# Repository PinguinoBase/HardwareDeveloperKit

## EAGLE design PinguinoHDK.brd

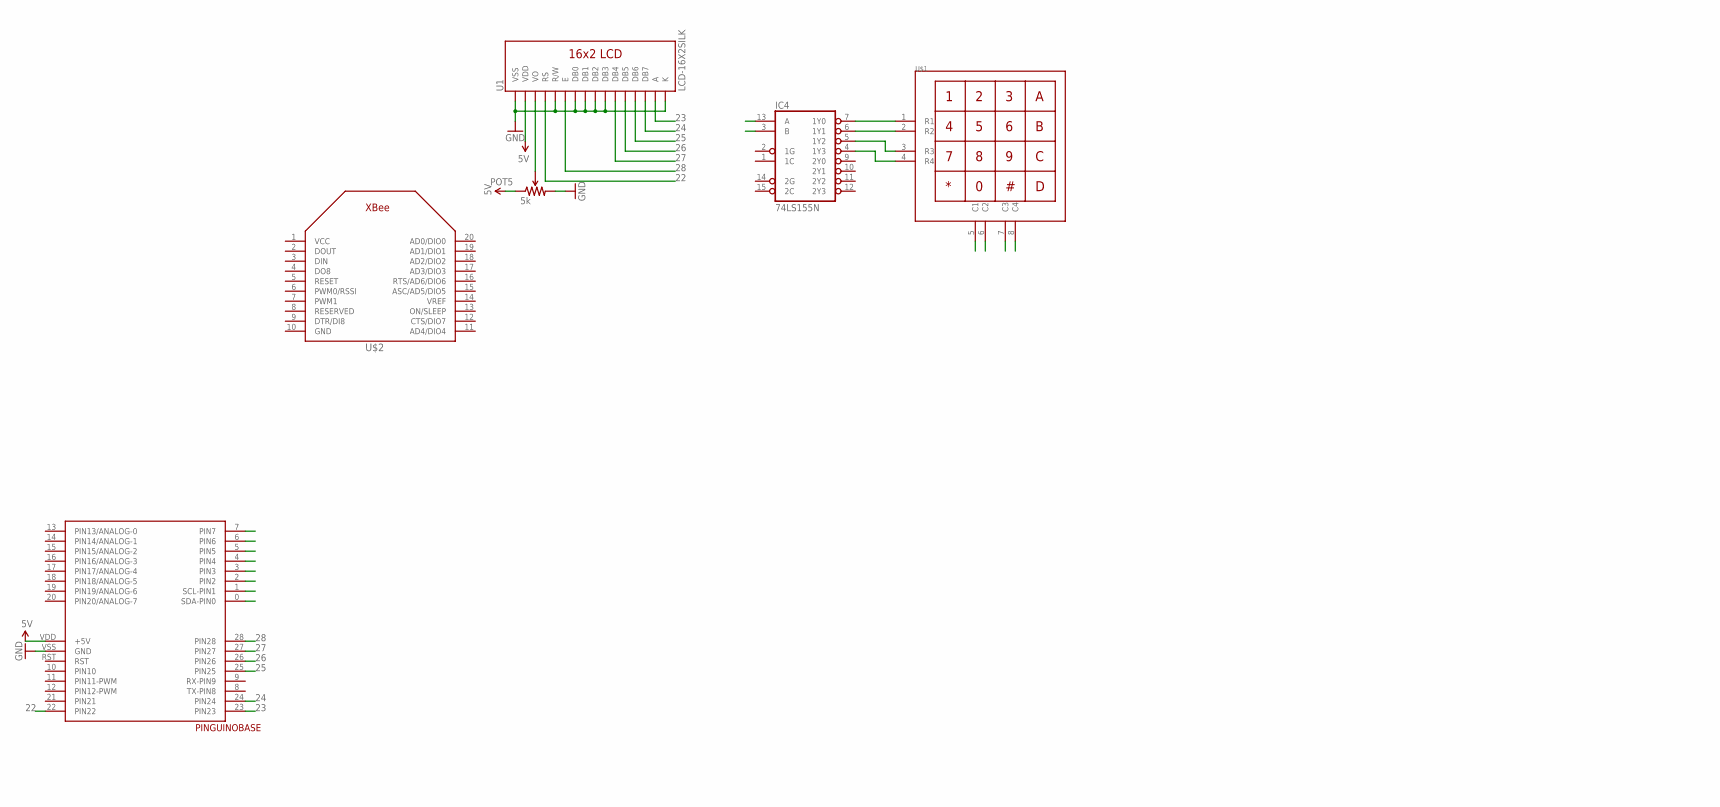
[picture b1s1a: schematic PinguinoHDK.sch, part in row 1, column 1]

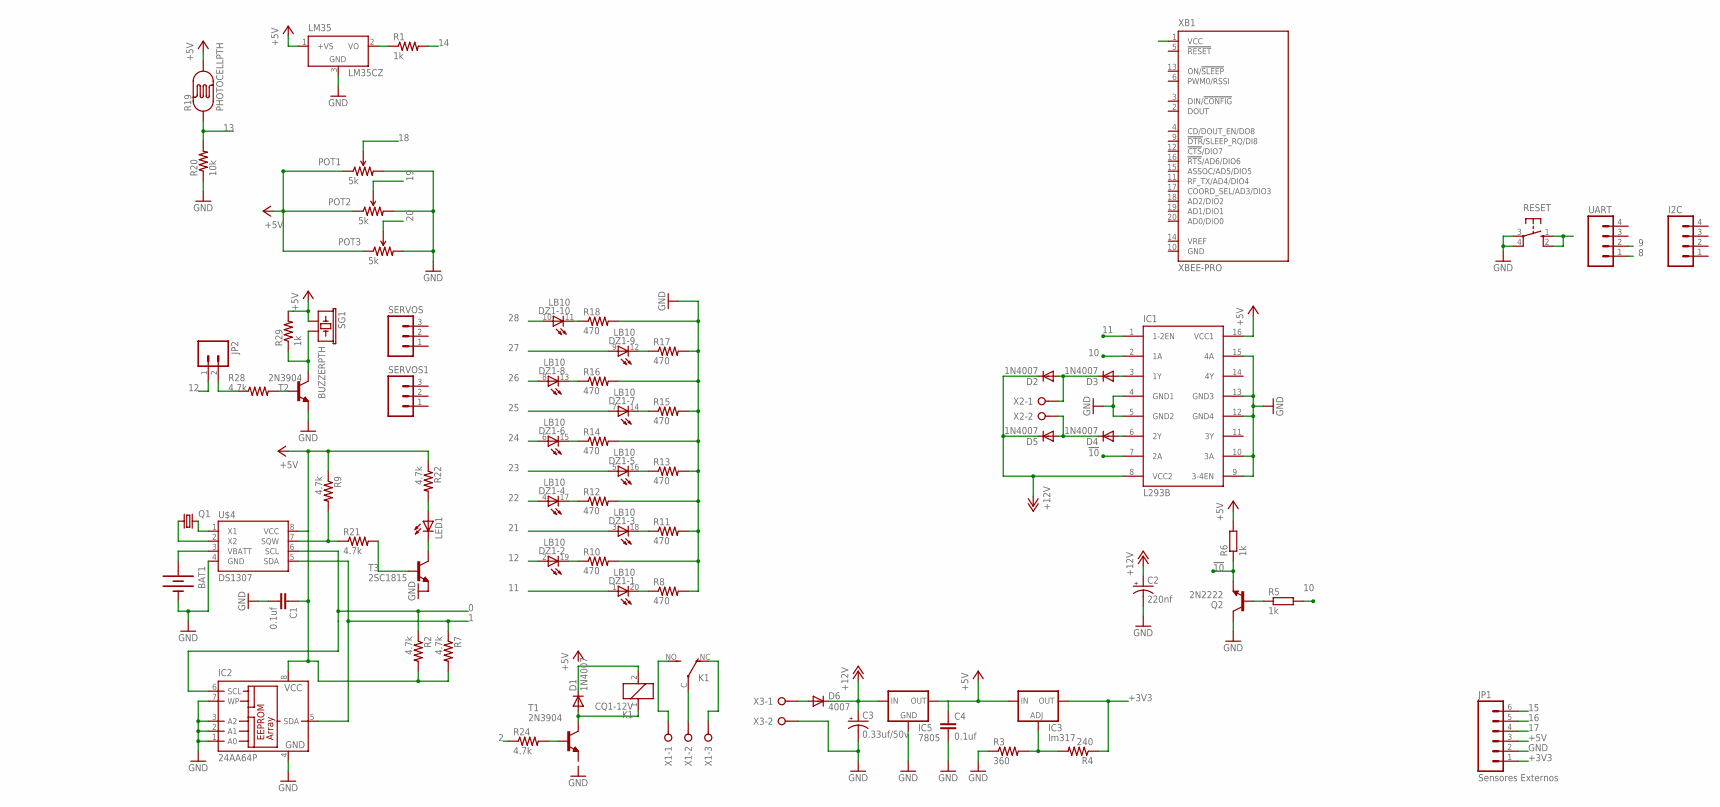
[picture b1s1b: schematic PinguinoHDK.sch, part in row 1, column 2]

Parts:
BAT1: BATTERY20PTH; BATTCOM_20MM_PTH
C1, C4: 0.1uf; CAP-PTH-SMALL2
C2: 220nf; CPOL-RADIAL-10UF-25V
C3: 0.33uf/50v; CPOL-RADIAL-10UF-25V
D1: 1N4007; DO41-10
D2, D3, D4, D5: 1N4007; DO35-7
D6: 4007; DO35-7
DZ1: LB10
I2C: M04LONGPADS; 1X04_LONGPADS
IC1: L293B; DIL16
IC2: 24AA64P; DIL8
IC3: lm317; 317TL
IC4: 74LS155N; DIL16
IC5: 7805; 78XXL
JP1: Sensores Externos; 1X06_LONGPADS
JP2: M02PTH3; 1X02_LONGPADS
K1: CQ1-12V; CQ1
LED1: LED3MM
LM35: LM35CZ; TO92
PINGUINOBASE: PINGUINOBASEFACEDOWN; FACEDOWN
POT1, POT2, POT3, POT5: 5k; TRIM_POT_PTH
Q1: CRYSTALTC38H; TC38H
Q2: 2N2222; TO-92
R1, R29: 1k; AXIAL-0.3-KIT
R2, R7, R9, R21, R22, R24, R28: 4.7k; AXIAL-0.3-KIT
R3: 360; AXIAL-0.3-KIT
R4: 240; AXIAL-0.3-KIT
R5, R6: 1k; 0204/7
R8, R10, R11, R12, R13, R14, R15, R16, R17, R18: 470; AXIAL-0.3-KIT
R19: PHOTOCELLPTH; PHOTOCELL
R20: 10k; 0204/5@1
RESET: 10-XX; B3F-10XX
SERVOS, SERVOS1: M03LONGPADS; 1X03_LONGPADS
SG1: BUZZERPTH; BUZZER-12MM
T1, T2: 2N3904; TO92
T3: 2SC1815; TO92-ECB
U1: LCD-16X2SILK; LCD-16X2
U$1: KEYPAD4X4
U$2: XBEE
U$4: DS1307; PDIP8
UART: M04LONGPADS; 1X04_LONGPADS
X1: W237-3E
X2, X3: W237-02P; W237-132
XB1: XBEE-PRO

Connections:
0: IC2.6 (SCL), PINGUINOBASE.0 (SDA-PIN0), R2.P$1 (1), U$4.6 (SCL)
1: IC2.5 (SDA), PINGUINOBASE.1 (SCL-PIN1), R7.P$1 (1), U$4.5 (SDA)
2: IC4.3 (B), PINGUINOBASE.2 (PIN2), R24.P$1 (1)
3: IC4.13 (A), PINGUINOBASE.3 (PIN3)
4: PINGUINOBASE.4 (PIN4), U$1.5 (C1)
5: PINGUINOBASE.5 (PIN5), U$1.6 (C2)
5V: PINGUINOBASE.VDD (+5V), POT5.1 (CCW), U1.2 (VDD)
6: PINGUINOBASE.6 (PIN6), U$1.7 (C3)
7: PINGUINOBASE.7 (PIN7), U$1.8 (C4)
8: UART.1
9: UART.2
10: IC1.2 (1A), R5.2
11: DZ1.1 (A), IC1.1 (1-2EN)
12: DZ1.2 (A), JP2.1
13: R19.1, R20.2
14: R1.P$2 (2)
15: JP1.6
16: JP1.5
17: JP1.4
18: POT1.2 (WIPER)
19: POT2.2 (WIPER)
20: POT3.2 (WIPER)
21: DZ1.3 (A)
22: DZ1.4 (A), PINGUINOBASE.22 (PIN22), U1.4 (RS)
23: DZ1.5 (A), PINGUINOBASE.23 (PIN23), U1.15 (A)
24: DZ1.6 (A), PINGUINOBASE.24 (PIN24), U1.14 (DB7)
25: DZ1.7 (A), PINGUINOBASE.25 (PIN25), U1.13 (DB6)
26: DZ1.8 (A), PINGUINOBASE.26 (PIN26), U1.12 (DB5)
27: DZ1.9 (A), PINGUINOBASE.27 (PIN27), U1.11 (DB4)
28: DZ1.10 (A), PINGUINOBASE.28 (PIN28), U1.6 (E)
!10: IC1.7 (2A), Q2.1 (E), R6.1
+3V3: IC3.2 (OUT), JP1.1, R4.P$1 (1), XB1.1 (VCC)
+5V: C1.1, C4.1, IC1.16 (VCC1), IC2.8 (VCC), IC3.3 (IN), IC5.OUT, JP1.3, LM35.1 (+VS), POT1.1 (CCW), POT2.1 (CCW), POT3.1 (CCW), R2.P$2 (2), R6.2, R7.P$2 (2), R9.P$1 (1), R19.2, R22.P$1 (1), R29.P$2 (2), SG1.+ (1), U$4.8 (VCC)
+12V: C2.1 (+), C3.1 (+), D2.C, D5.C, D6.C, IC1.8 (VCC2), IC5.IN
GND: BAT1.2 (-), C1.2, C2.2 (-), C3.2 (-), C4.2, IC1.4 (GND1), IC1.5 (GND2), IC1.9 (3-4EN), IC1.10 (3A), IC1.12 (GND4), IC1.13 (GND3), IC1.15 (4A), IC2.1 (A0), IC2.2 (A1), IC2.3 (A2), IC2.4 (GND), IC2.7 (WP), IC4.8 (GND), IC5.GND, JP1.2, LM35.3 (GND), PINGUINOBASE.VSS (GND), POT1.3 (CW), POT2.3 (CW), POT3.3 (CW), POT5.3 (CW), Q2.3 (C), R3.P$1 (1), R8.P$2 (2), R10.P$2 (2), R11.P$2 (2), R12.P$2 (2), R13.P$2 (2), R14.P$2 (2), R15.P$2 (2), R16.P$2 (2), R17.P$2 (2), R18.P$2 (2), R20.1, RESET.3, RESET.4 (P1), T2.3 (E), T3.E, U1.1 (VSS), U1.5 (R/W), U1.7 (DB0), U1.8 (DB1), U1.9 (DB2), U1.10 (DB3), U1.16 (K), U$4.4 (GND), X3.2, XB1.10 (GND)
unnamed: LM35.2 (VO), R1.P$1 (1)
unnamed: Q1.2, U$4.1 (X1)
unnamed: Q1.1, U$4.2 (X2)
unnamed: BAT1.1 (+), U$4.3 (VBATT)
unnamed: POT5.2 (WIPER), U1.3 (VO)
unnamed: IC3.1 (ADJ), R3.P$2 (2), R4.P$2 (2)
unnamed: K1.C, X1.2
unnamed: K1.NC (O), X1.3
unnamed: K1.NO (S), X1.1
unnamed: R24.P$2 (2), T1.2 (B)
unnamed: R28.P$2 (2), T2.2 (B)
unnamed: D1.A, K1.1, T1.1 (C)
unnamed: R29.P$1 (1), SG1.- (2), T2.1 (C)
unnamed: JP2.2, R28.P$1 (1)
unnamed: D3.A, IC1.3 (1Y)
unnamed: D4.A, IC1.6 (2Y)
unnamed: D4.C, D5.A, X2.2
unnamed: D2.A, D3.C, X2.1
unnamed: D6.A, X3.1
unnamed: DZ1.18 (C), R11.P$1 (1)
unnamed: DZ1.16 (C), R13.P$1 (1)
unnamed: DZ1.20 (C), R8.P$1 (1)
unnamed: DZ1.19 (C), R10.P$1 (1)
unnamed: DZ1.17 (C), R12.P$1 (1)
unnamed: DZ1.15 (C), R14.P$1 (1)
unnamed: DZ1.14 (C), R15.P$1 (1)
unnamed: DZ1.13 (C), R16.P$1 (1)
unnamed: DZ1.12 (C), R17.P$1 (1)
unnamed: DZ1.11 (C), R18.P$1 (1)
unnamed: LED1.A, R22.P$2 (2)
unnamed: R9.P$2 (2), R21.P$1 (1), U$4.7 (SQW)
unnamed: Q2.2 (B), R5.1
unnamed: R21.P$2 (2), T3.B
unnamed: LED1.K (C), T3.C
unnamed: D1.C, K1.2
unnamed: IC4.4 (1Y3), U$1.4 (R4)
unnamed: IC4.5 (1Y2), U$1.3 (R3)
unnamed: IC4.6 (1Y1), U$1.2 (R2)
unnamed: IC4.7 (1Y0), U$1.1 (R1)
RST: RESET.1 (S), RESET.2 (S1)
VCC: IC4.16 (VCC)

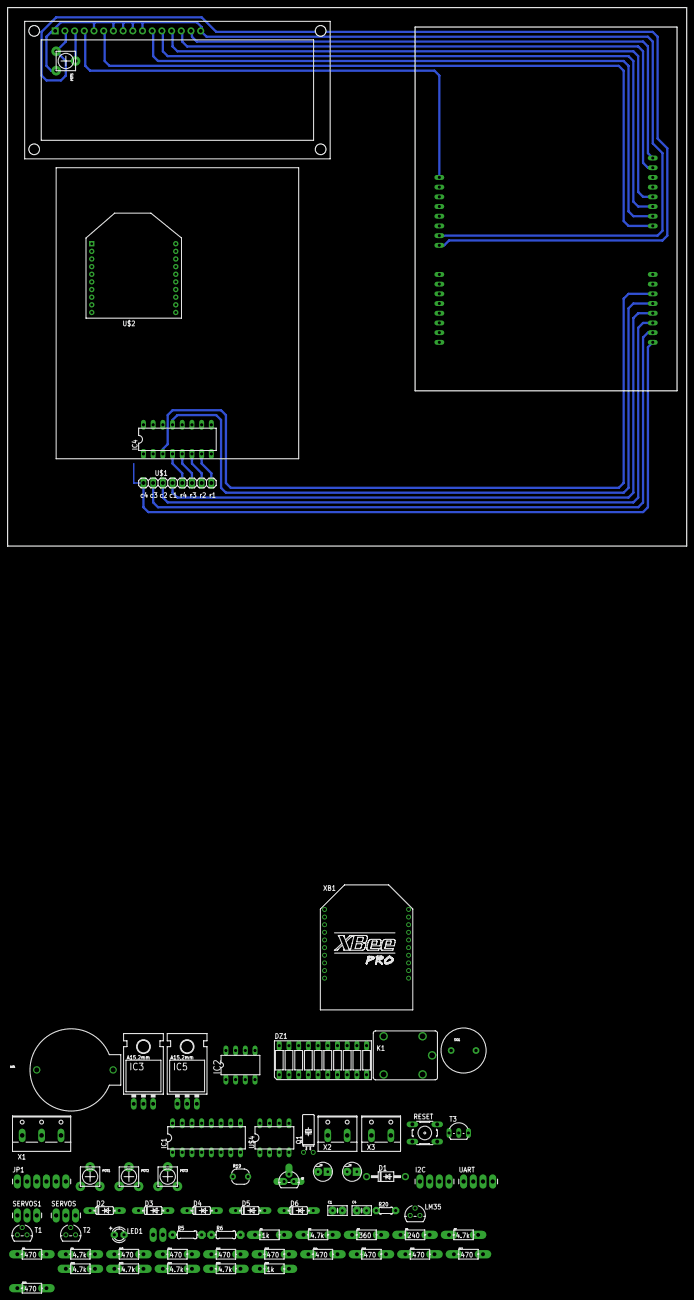
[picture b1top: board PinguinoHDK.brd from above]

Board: 2 copper layers, 177.8 x 141.0 mm, 71 parts (0 on the bottom side), 65 nets.

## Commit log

2012-11-08 Inicio de Proyecto
2012-11-08 Comienzo de Fuente de Alimentación
    Se comenzo a trabajar en la fuente de alimentación, esta esta diseñada
    bajo estrictos filtros, para maximizar su eficiencia, el esquematico ya
    esta diseñado solo falta la colocacion de los componentes en la placa
2013-02-14 Algunas actualizaciones al cableado de la lcd 16x2

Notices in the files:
parts and their libraries:
SparkFun: Licensing: CC v3.0 Share-Alike You are welcome to use this library for commercial purposes.
